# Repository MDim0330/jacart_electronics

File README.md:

**JACart Electronics Repo**

Contain Python and Arduino controller code for managing the Teleop board.

**Repo Contents**

cart_teleop_dac:/ Updated Arduino teleop code that utilizes DACs instead of PWM signals. This version should be the one used going forward.

python_teleop:/ Stand-alone python controller for teleop_board

libs:/ Require libraries for operating the Arudino teleop code

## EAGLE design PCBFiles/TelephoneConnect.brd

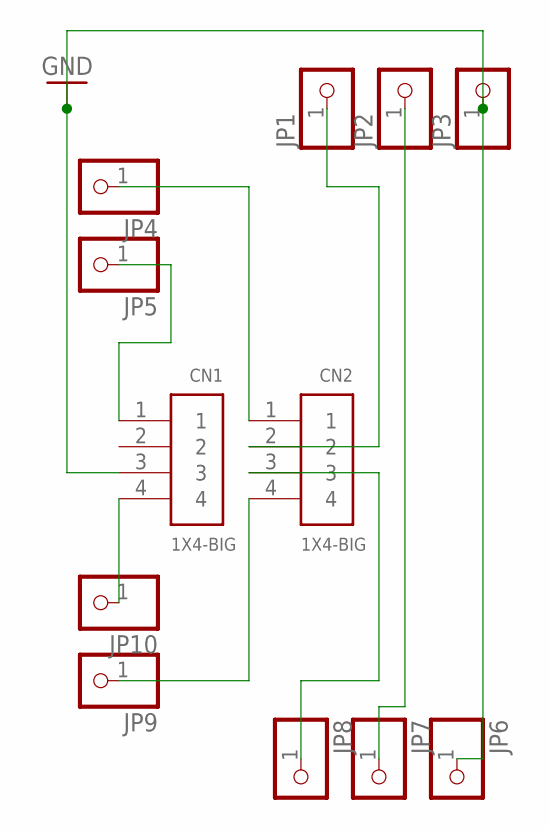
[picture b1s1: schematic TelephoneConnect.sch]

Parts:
CN1, CN2: 1X4-BIG; 1X04-BIG
JP1, JP2, JP3, JP4, JP5, JP6, JP7, JP8, JP9, JP10: PINHD-1X1; 1X01

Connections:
GND: CN1.3, JP3.1, JP6.1
unnamed: CN1.1, JP5.1
unnamed: CN2.1, JP4.1
unnamed: CN1.4, JP10.1
unnamed: CN2.4, JP9.1
unnamed: CN2.3, JP8.1
unnamed: CN2.2, JP1.1
unnamed: JP2.1, JP7.1

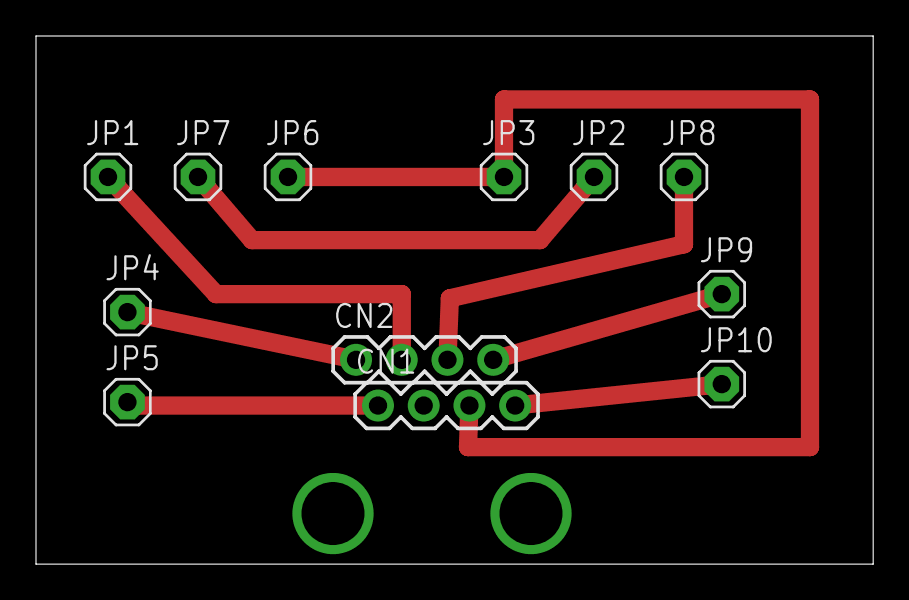
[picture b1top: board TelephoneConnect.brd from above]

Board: 2 copper layers, 46.5 x 29.3 mm, 12 parts (0 on the bottom side), 8 nets.

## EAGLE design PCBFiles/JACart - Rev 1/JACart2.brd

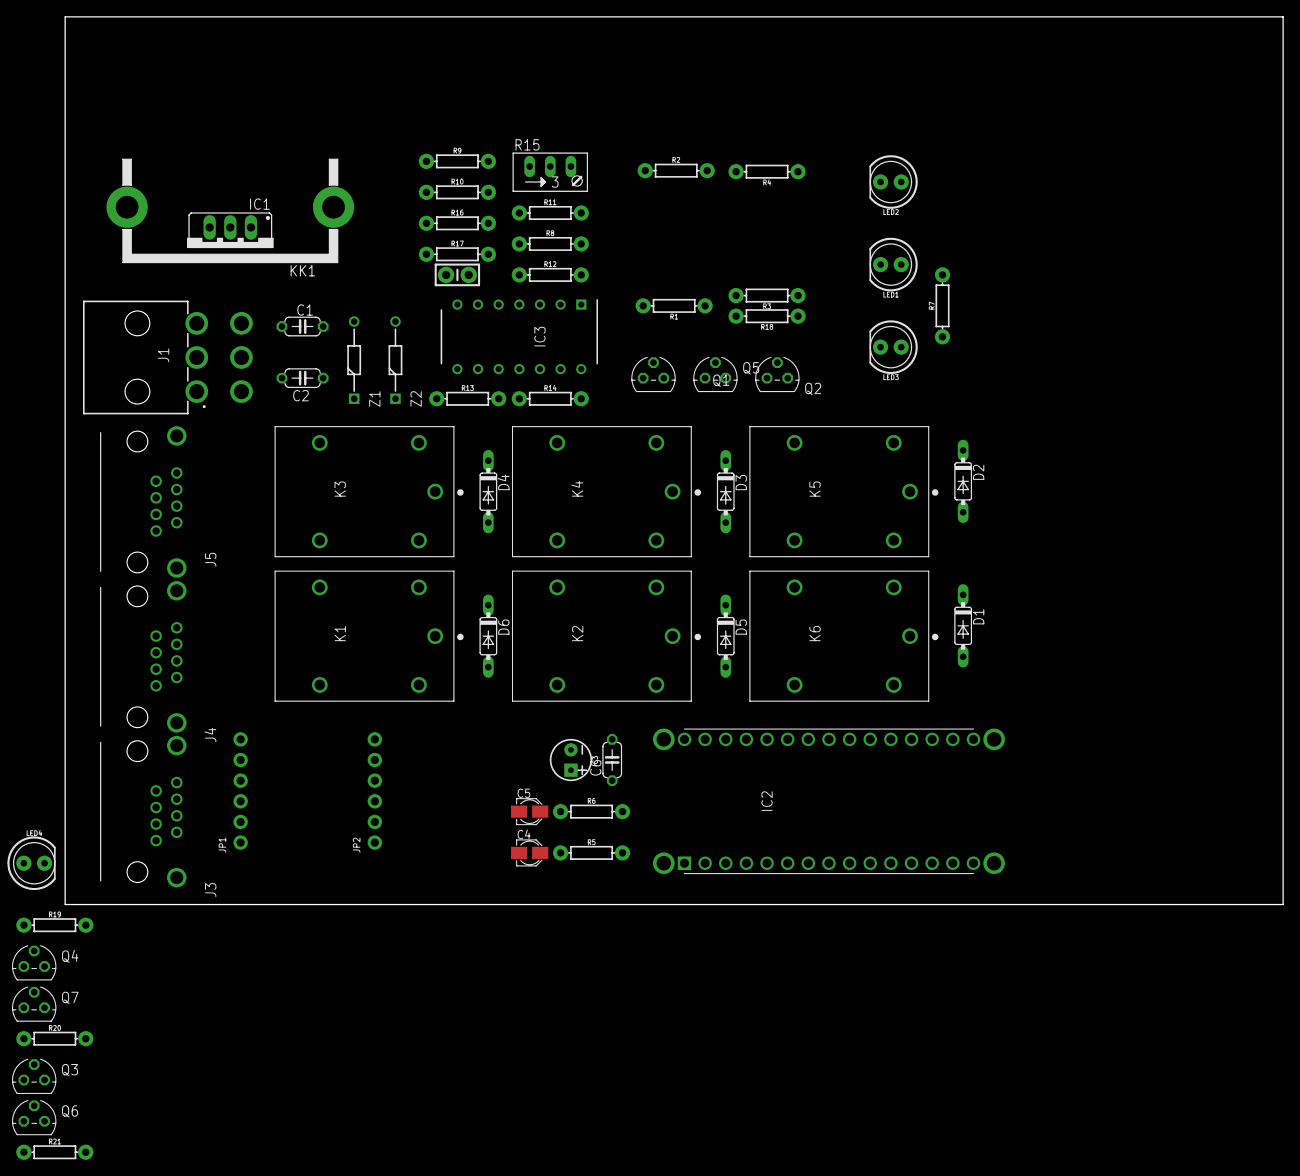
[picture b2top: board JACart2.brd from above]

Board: 2 copper layers, 149.9 x 109.2 mm, 63 parts (0 on the bottom side), 53 nets, no tracks yet.

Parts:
C1, C6: 0.1uF; C050-024X044
C2: 0.33uF; C050-024X044
C3: 10uF; CPOL-RADIAL-2.5MM-5MM
C4, C5: 330uF; PANASONIC_A
C7: 1.0uF; CAP-PTH-SMALL-KIT
D1, D2, D3, D4, D5, D6: 1N4148; DO35-7
IC1: LM7805; 78XXS
IC2: ARD-NANO30NP; ARDNANO30NP
IC3: LMC6484IN; DIP794W56P254L1905H533Q14N
J1: 39-30-1060; 39-30-1060_1
J3: Steering; GLX-S-88M
J4: Brake; GLX-S-88M
J5: Throttle; GLX-S-88M
JP1, JP2: MCP4725; 1X06_ROUND_70
K1: Brake(1); RELAY_JS1-5V-F
K2: Brake(2); RELAY_JS1-5V-F
K3: Throttle(3); RELAY_JS1-5V-F
K4: Throttle(4); RELAY_JS1-5V-F
K5: Throttle; RELAY_JS1-5V-F
K6: Brake; RELAY_JS1-5V-F
KK1: FK222
LED1: Brake; LED_5MM
LED2: Throttle; LED_5MM
LED3: Auto; LED_5MM
LED4: PANIC; LED_5MM
Q1, Q2, Q3, Q4, Q5, Q6, Q7: TO92
R1, R18, R20: 2.2k; AXIAL-0.3
R2, R4, R17: 1k; AXIAL-0.3
R3, R21: 160; AXIAL-0.3
R5, R6, R13: 220; AXIAL-0.3
R7: 820; AXIAL-0.3
R8: 1M; AXIAL-0.3
R9: 470; AXIAL-0.3
R10: TBD; AXIAL-0.3
R11, R12, R14: 10k; AXIAL-0.3
R15: 1k; RJ9W
R16: 100; AXIAL-0.3
R19: 330; AXIAL-0.3
Z1, Z2: BAT85S-TR; DIOAD950W60L350D150

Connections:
5V: C1.1, C3.1, C6.1, D1.C, D2.C, IC1.OUT, IC2.19, J1.2, J1.5, J3.2, JP1.1, JP2.1, JP2.5, K5.2, K6.2, Q3.1, Q4.1, R3.P$1, R21.P$1
AUTO: D3.C, D4.C, D5.C, D6.C, J1.3, K1.2, K2.2, K3.2, K4.2, R7.P$1
BKA: IC2.11, R2.P$2
BRKSIG: K1.3, Z1.1, Z2.1
GND: C1.2, C2.2, C3.2, C4.-, C5.-, C6.2, D3.A, D4.A, D5.A, D6.A, IC1.GND, IC2.4, IC2.17, IC3.11, J1.1, J3.3, J4.3, J5.3, JP1.2, JP2.2, K1.5, K2.5, K3.5, K4.5, KK1.A2,8, KK1.B2,8, LED3.K, LED4.K, Q1.3, Q2.3, Q5.3, Q6.3, Q7.3, R9.P$1, R13.P$1, R15.A
unnamed: C2.1, IC1.IN, J1.4
unnamed: D1.A, K6.5, Q1.1
unnamed: Q2.2, Q4.3
unnamed: LED3.A, R7.P$2
unnamed: Q4.2, Q5.1, R4.P$1, R20.P$1
unnamed: LED2.A, R3.P$2
unnamed: LED2.K, Q7.1
unnamed: Q1.2, Q3.3
unnamed: IC2.9, R6.P$2
unnamed: IC2.8, R5.P$2
unnamed: Q3.2, R1.P$1, R2.P$1
unnamed: D2.A, K5.5, Q2.1
unnamed: J5.4, K3.4
unnamed: R9.P$2, R10.P$2, R12.P$1, R16.P$2
unnamed: K2.3, K6.3
unnamed: K4.3, K5.3
unnamed: J5.7, K5.1
unnamed: J5.8, K4.1
unnamed: J5.2, K4.4
unnamed: J5.6, K3.1
unnamed: J4.7, K6.1
unnamed: J4.8, K2.1
unnamed: J4.2, K2.4
unnamed: J4.6, K1.1
unnamed: J4.4, K1.4
unnamed: IC3.1, R8.P$2, R12.P$2
unnamed: IC3.2, R8.P$1, R11.P$1
unnamed: IC3.5, IC3.13, IC3.14, R16.P$1
unnamed: IC3.12, R13.P$2, R14.P$1
unnamed: R11.P$2, R15.S
unnamed: IC3.6, R10.P$1, R17.P$2
unnamed: C7.1, IC3.7, Z2.2
unnamed: C7.2, R17.P$1
unnamed: C5.+, R6.P$1, Z1.2
unnamed: Q5.2, R18.P$1
unnamed: LED4.A, R19.P$1
unnamed: Q7.2, R20.P$2
unnamed: LED1.K, Q6.1
unnamed: LED1.A, R21.P$2
unnamed: Q6.2, R1.P$2
PANIC: IC2.5, IC3.4, J1.6, R14.P$2, R15.E, R18.P$2, R19.P$2
POTWPR: IC2.27, J3.1
SCL: IC2.22, JP1.3, JP2.3
SDA: IC2.23, JP1.4, JP2.4
STRLFT: IC2.13, J3.8, JP2.6
STRRT: IC2.12, J3.7, JP1.6
TLA: IC2.10, R4.P$2
TTLSIG: C4.+, K3.3, R5.P$1

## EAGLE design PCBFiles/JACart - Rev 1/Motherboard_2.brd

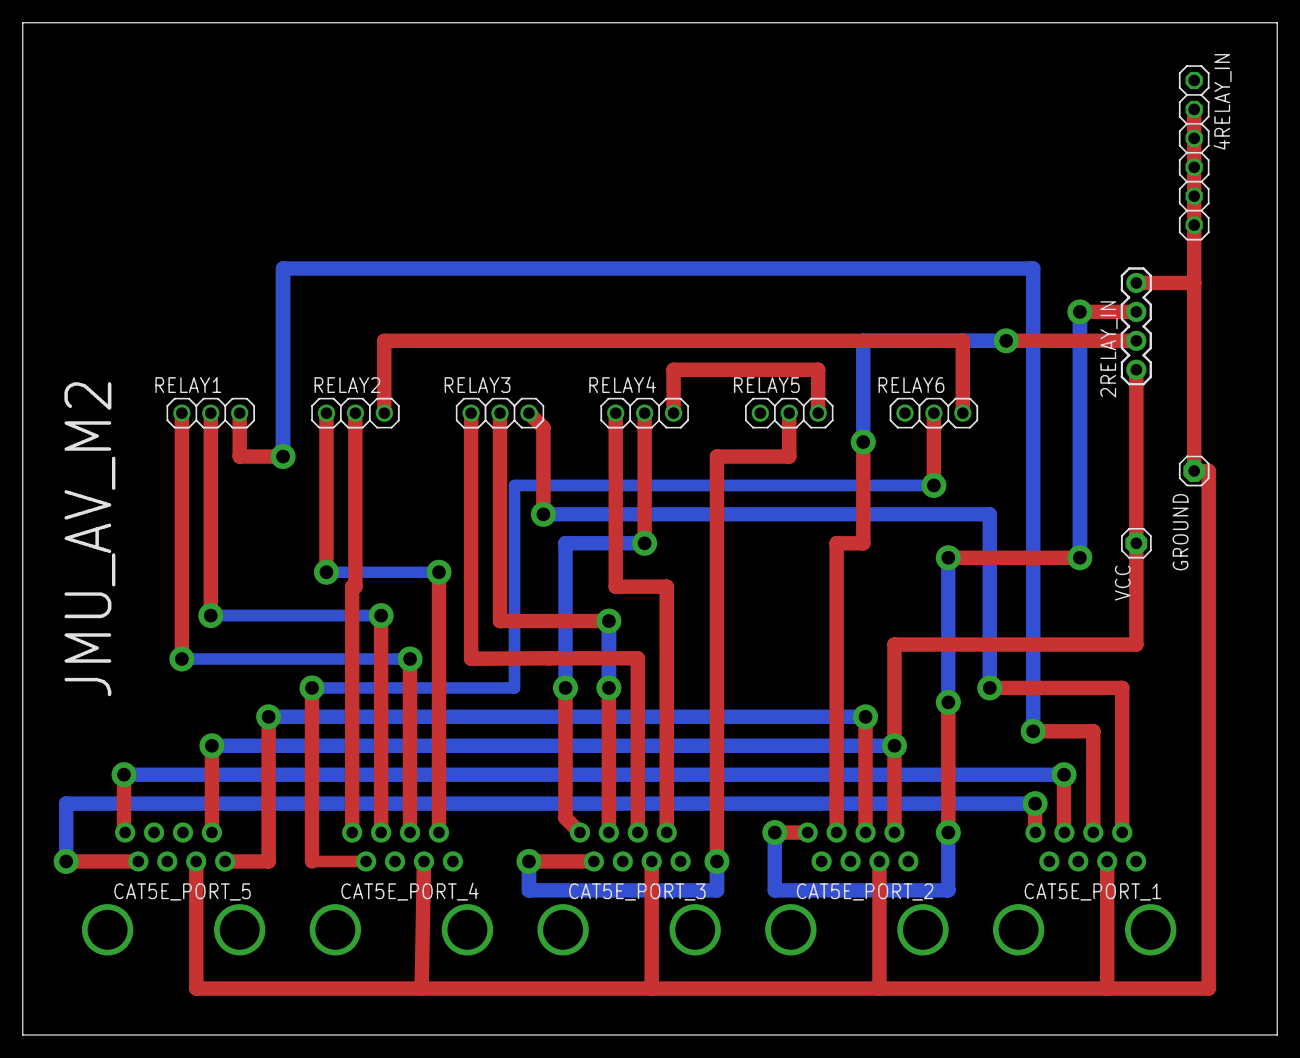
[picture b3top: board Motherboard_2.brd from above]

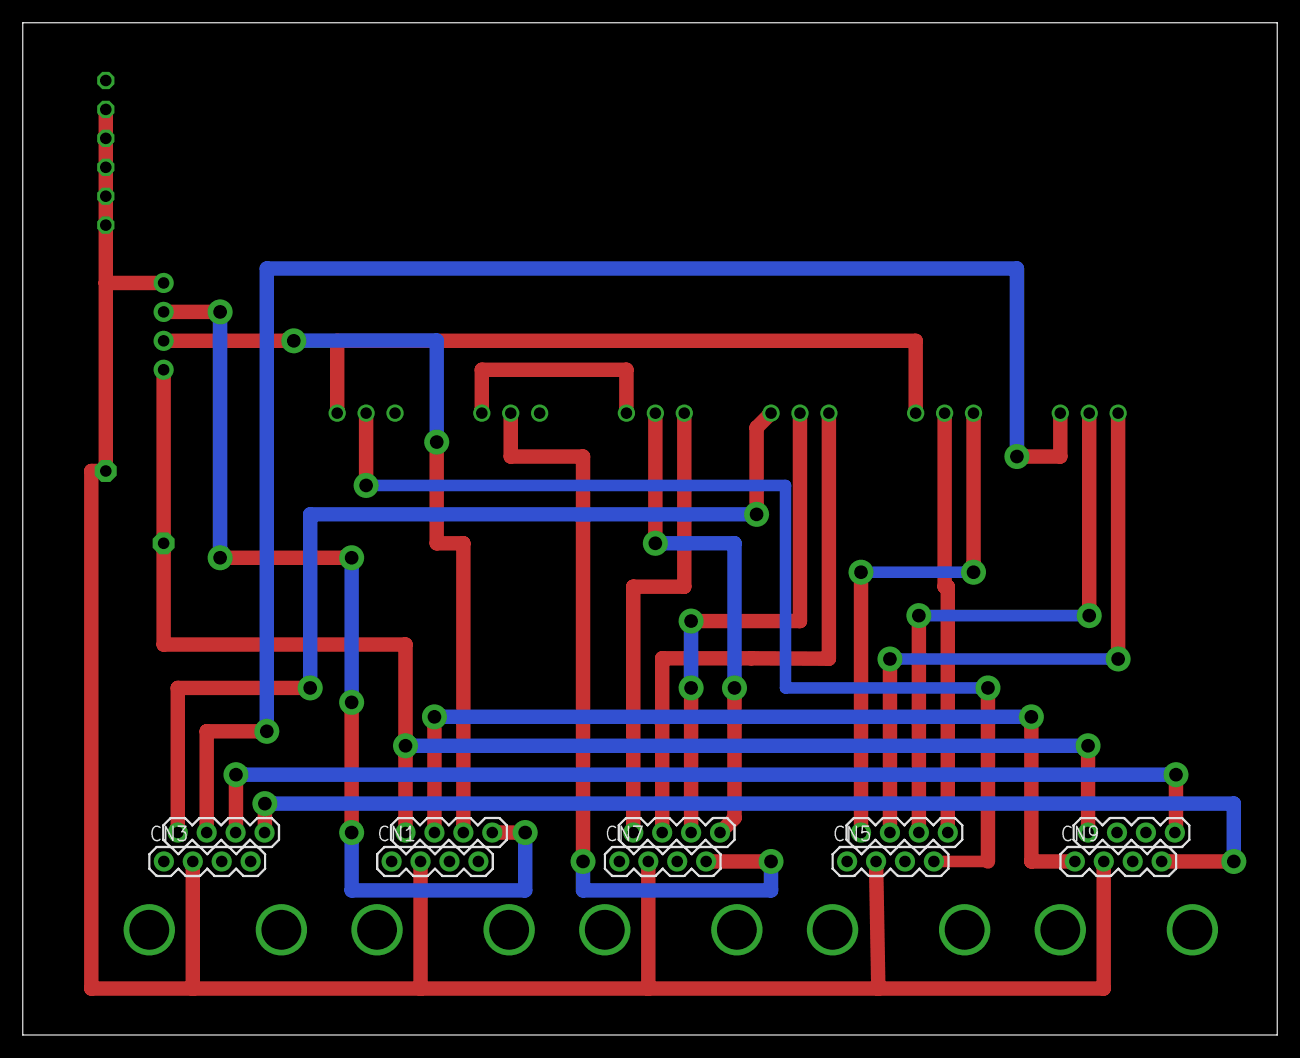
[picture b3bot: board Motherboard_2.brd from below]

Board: 2 copper layers, 110.2 x 88.9 mm, 20 parts (10 on the bottom side), 21 nets.

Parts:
2RELAY_IN: 1X4-BIG; 1X04-BIG
4RELAY_IN: 1X06
CAT5E_PORT_1, CAT5E_PORT_2, CAT5E_PORT_3, CAT5E_PORT_4, CAT5E_PORT_5: 1X4-BIG; 1X04-BIG
CN1, CN3, CN5, CN7, CN9: 1X4-BIG; 1X04-BIG
GROUND: 1X01
RELAY1, RELAY2, RELAY3, RELAY4, RELAY5, RELAY6: 1X03
VCC: 1X01

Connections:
unnamed: CAT5E_PORT_4.1, RELAY2.1
unnamed: CAT5E_PORT_4.2, RELAY1.1
unnamed: CAT5E_PORT_4.3, RELAY1.2
unnamed: CAT5E_PORT_4.4, RELAY2.2
unnamed: CN5.4, RELAY6.2
unnamed: 2RELAY_IN.3, CAT5E_PORT_2.4
unnamed: CAT5E_PORT_3.1, RELAY4.1
unnamed: CAT5E_PORT_3.2, RELAY3.1
unnamed: CAT5E_PORT_3.4, RELAY4.2
unnamed: RELAY2.3, RELAY6.3
unnamed: RELAY4.3, RELAY5.3
unnamed: CN7.4, RELAY5.2
unnamed: CAT5E_PORT_1.1, RELAY3.3
unnamed: CAT5E_PORT_3.3, RELAY3.2
unnamed: CAT5E_PORT_1.2, RELAY1.3
unnamed: CAT5E_PORT_1.3, CAT5E_PORT_5.4
unnamed: CAT5E_PORT_1.4, CN9.4
unnamed: CAT5E_PORT_2.2, CN9.1
unnamed: 2RELAY_IN.1, CAT5E_PORT_2.1, CAT5E_PORT_5.1, VCC.1
unnamed: 2RELAY_IN.4, 4RELAY_IN.2, 4RELAY_IN.3, 4RELAY_IN.4, 4RELAY_IN.5, 4RELAY_IN.6, CN1.2, CN3.2, CN5.2, CN7.2, CN9.2, GROUND.1
unnamed: 2RELAY_IN.2, CAT5E_PORT_2.3

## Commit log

2019-10-29 Add existing files
2019-11-19 v2.0
2020-06-03 commit of current arduino code
2020-08-19 fix binary format.
2020-08-19 remove some prints
2020-09-01 fix baud rate
2020-09-20 fix for python3
2020-09-20 improve reliability of serial reading
2020-09-20 fix bug
2020-10-18 add and rename teleop to this repo
2020-10-21 changed usb port to '/dev/ttyUSB9'
2020-11-05 Upload schematic of current controller board schematics
2020-11-11 new dac version
2020-11-12 Ignore my dev environment files
2020-11-12 Update comments
2020-11-12 Add libs folder to hold Arduino teleop libraries
2020-11-12 Deprecate old PWM teleop board
2020-11-17 Copy in Arduino libraries from local install
2020-11-24 Remove bad libraries folder
2020-11-24 Commenting and dead code removal
2020-11-24 Add requirements file to ensure correct packages are installed
2020-12-09 Add author tag
2021-01-21 Create install and run scripts for Python environment
2021-01-21 Add heartbeat and silence all prints
2021-01-21 Create PCBFiles
2021-01-21 Added Dick's PCB Files
    PCB Designs
2021-02-09 Add golf cart wiring diagrams
2021-03-08 Adding additional Eagle design files
2021-03-08 Add gitignore file
2021-03-08 Re-organize and delete hidden files
2021-03-29 Add in missing libs
2021-04-29 Resolve braking error and reduce verbosity
2021-05-06 Add abs() to ensure we avoid overflow errors
2021-06-01 Enable teleop to scan for correct port on MacOS
2021-06-02 Add diagnostic version
2021-06-15 Add Jorge documentation
2021-06-15 Clarify teleop comments
2021-06-16 Update chart schematics
2022-04-12 Add in missing Library
2022-05-12 updated PIDs for steering for Comm Circuit Board v1.0
2022-05-12 Added in CommBoardPCBFiles (new all-in-one board)
2022-06-15 Update cart_teleop_dac.ino
    KD value changed from 1.0 to 1.19
2022-06-16 New anolog port read and write
